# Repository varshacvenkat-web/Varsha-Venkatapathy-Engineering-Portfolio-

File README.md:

# Varsha-Venkatapathy-Engineering-Portfolio-
Portfolio of all projects done through my undergraduate and industry career:

**Biomedical Engineering | Machine Learning | Medical Device Innovation**

Portfolio of technical projects spanning **medical device development**, **deep learning applications**, and **hardware-embedded systems**. Work includes NSF-funded ultrasound imaging research, competitive scholarship projects, industry ML deployment, and FDA-pathway medical devices—demonstrating expertise across the full engineering stack from signal processing to production-ready systems.

**Highlights:**
-  **Medical Devices**: Self-charging pacemaker systems, real-time load monitoring for scoliosis treatment
-  **Machine Learning**: LSTM revenue forecasting (industry deployment), speech enhancement, medical image processing
-  **Research**: NSF-funded ultrasound imaging, Abrams Scholar project, multi-lab publications

*MS ECE Applicant | UNC Chapel Hill & NC State BME '25*

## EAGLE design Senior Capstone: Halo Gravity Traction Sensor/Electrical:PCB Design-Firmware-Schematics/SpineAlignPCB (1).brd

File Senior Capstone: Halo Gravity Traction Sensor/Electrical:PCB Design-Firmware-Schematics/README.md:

## Electrical, PCB Design, Firmware, and Schematics  
## Senior Capstone: Halo Gravity Traction Load Monitoring Device

This directory contains all electrical engineering components of the halo gravity traction load-monitoring system, including schematics, PCB design files, firmware, and reference circuit images. These files document the full electrical workflow from concept to implementation.

---

## Contents

## Electrical Schematic
**File:** Electrical Schematic.pdf  
A complete wiring diagram detailing all electrical connections for the load monitoring device.  
Includes:
- Load cell interface  
- HX711 amplifier wiring  
- Microcontroller I/O assignments  
- Power regulation and battery connections  
- Safety components and grounding strategy  

---

## Firmware
**File:** Fullcodefinal_copy_20250424150533.ino  
The final microcontroller firmware used to:
- Read load cell data via HX711  
- Apply calibration factors  
- Perform real-time signal filtering  
- Stream traction load to external devices  
- Log sensor values for testing and verification  

Written in Arduino C/C++ for rapid prototyping and device testing.

---

## PCB Design Files
These files correspond to the custom PCB developed for the traction load-monitoring system.

### Board Layout  
**File:** SpineAlignPCB (1).brd  
Includes:
- Component placement  
- Routing of analog and digital traces  
- Ground plane and power distribution  
- Mounting hole alignment for enclosure  

### Schematic Source  
**File:** SpineAlignPCB (1).sch  
Editable schematic source file for PCB manufacturing or revision.

---

## Reference Circuit Image
**File:** circuit (2).png  
Circuit image used during early prototyping and breadboard validation.  
Shows:
- Preliminary load cell + amplifier wiring  
- Pin mapping for MCU  
- Initial design considerations prior to final PCB creation  

---

## Design Considerations

### Signal Integrity
- Short trace lengths for low-noise analog signals  
- Dedicated analog ground routing  
- Shielding and filtering for load cell signals  

### Power Management
- Battery-powered operation  
- Onboard voltage regulation  
- Low-power microcontroller configuration  

### Safety and Reliability
- Reverse-polarity protection  
- Overcurrent considerations  
- Mechanical strain relief for cable connections  

---

## Firmware Overview

### Main Functions
- `readLoadCell()`: Retrieves calibrated weight values  
- `tare()`: Zeros load cell drift  
- `HX711.begin()`: Initializes ADC amplifier  
- `Serial.write()`: Streams continuous load values  

### Sampling Rate
Configured for stable real-time data acquisition without significant lag.

---

## Recommended Tools

To edit or view files:
- **EAGLE or KiCad** — for PCB `.brd` / `.sch` files  
- **Arduino IDE** — for `.ino` firmware  
- **Adobe/Preview** — to view PDF schematics  
- **Any image viewer** — for `.png` circuit references  

---

## Usage Guide

1. Review the Electrical Schematic for wiring details  
2. Use PCB files for manufacturing or revisions  
3. Flash firmware to microcontroller using Arduino IDE  
4. Validate sensor readings with circuit reference image  
5. Integrate PCB into mechanical enclosure

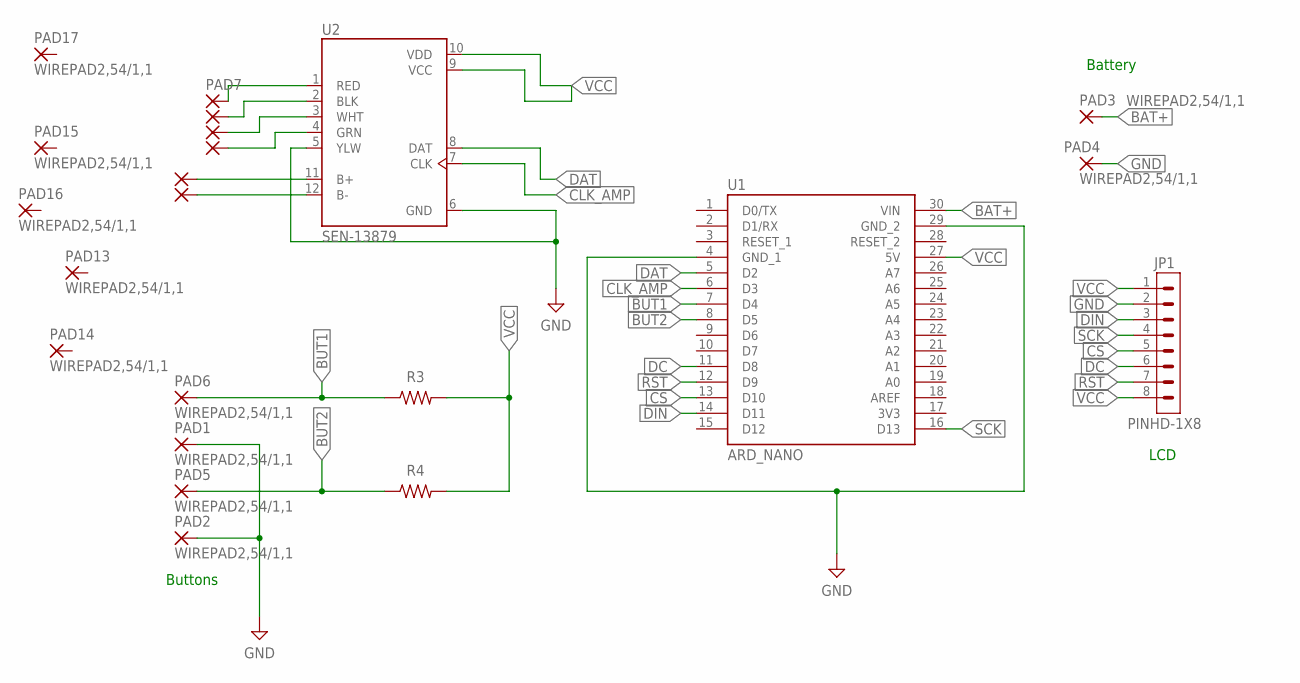
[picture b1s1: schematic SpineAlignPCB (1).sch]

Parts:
JP1: PINHD-1X8; 1X08
PAD1, PAD2, PAD3, PAD4, PAD5, PAD6, PAD7, PAD8, PAD9, PAD10, PAD11, PAD12, PAD13, PAD14, PAD15, PAD16, PAD17: WIREPAD2,54/1,1; 2,54/1,1
R3, R4: R-US_AXIAL-11.7MM-PITCH; RESAD1176W63L850D250B
U1: ARD_NANO; MODULE_A000005
U2: SEN-13879; SPARKFUN_SEN-13879

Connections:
3V3: U1.17 (3V3)
BAT+: PAD3.1, U1.30 (VIN)
BUT1: PAD6.1, R3.1, U1.7 (D4)
BUT2: PAD5.1, R4.1, U1.8 (D5)
CLK_AMP: U1.6 (D3), U2.7 (CLK)
CS: JP1.5, U1.13 (D10)
DAT: U1.5 (D2), U2.8 (DAT)
DC: JP1.6, U1.11 (D8)
DIN: JP1.3, U1.14 (D11)
GND: JP1.2, PAD1.1, PAD2.1, PAD4.1, U1.4 (GND_1), U1.29 (GND_2), U2.5 (YLW), U2.6 (GND)
unnamed: PAD7.1, U2.1 (RED)
unnamed: PAD8.1, U2.2 (BLK)
unnamed: PAD9.1, U2.3 (WHT)
unnamed: PAD10.1, U2.4 (GRN)
unnamed: PAD11.1, U2.11 (B+)
unnamed: PAD12.1, U2.12 (B-)
RST: JP1.7, U1.12 (D9)
SCK: JP1.4, U1.16 (D13)
VCC: JP1.1, JP1.8, R3.2, R4.2, U1.27 (5V), U2.9 (VCC), U2.10 (VDD)

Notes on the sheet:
LCD
Buttons
Battery

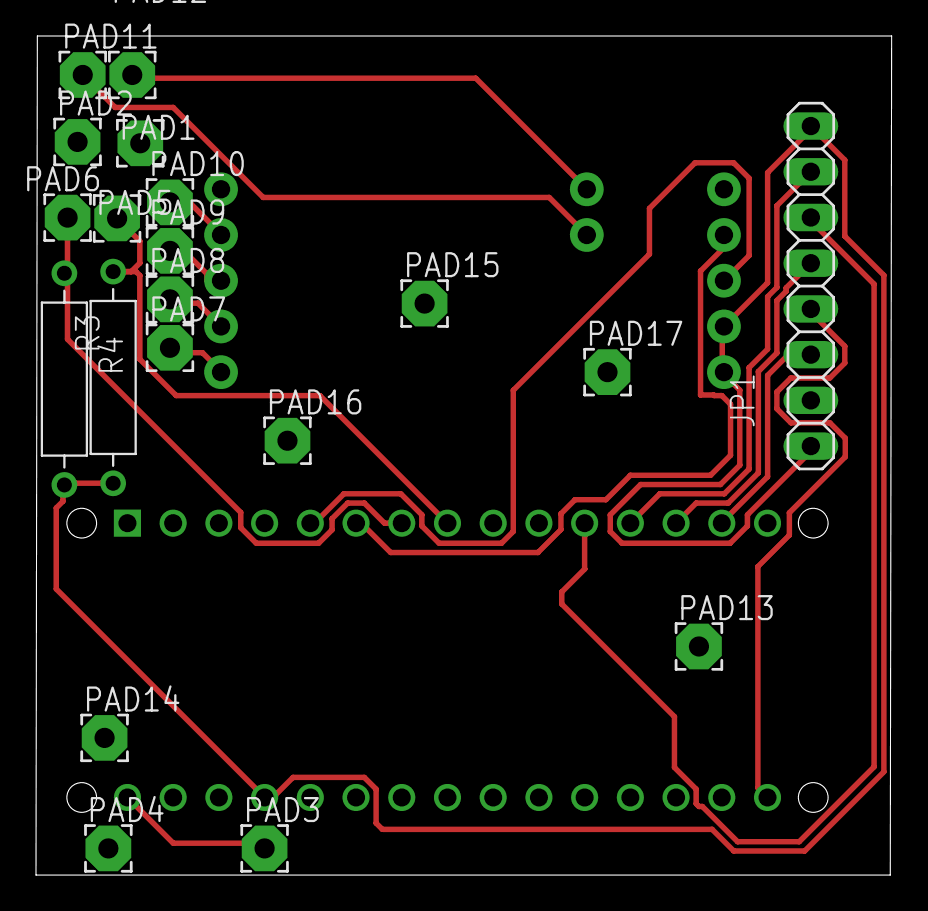
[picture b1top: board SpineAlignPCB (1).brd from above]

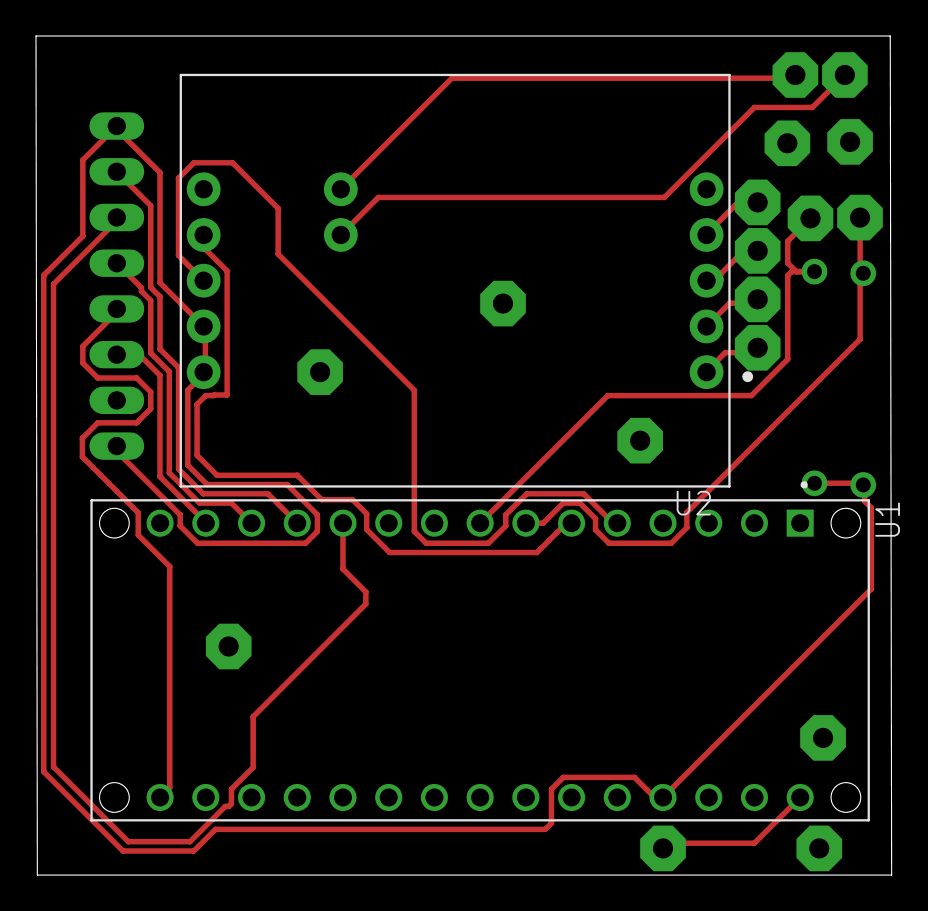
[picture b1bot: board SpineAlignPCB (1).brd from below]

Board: 2 copper layers, 47.5 x 46.6 mm, 22 parts (2 on the bottom side), 18 nets.

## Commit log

2025-11-26 Enhance README with project details and achievements
    Added detailed project overview, key achievements, technical implementation, preliminary results, and research impact sections to README.
2025-11-26 Created using Colab
2025-11-26 Rename Ultrasound_Tumor_Detection_Code_.ipynb to bmme-590-ultrasound/ Ultrasound_Tumor_Detection_Code_ipynb
2025-11-26 Create Deep Learning Speech Enhancement Abrams Scholar Project
2025-11-26 Add project overview for speech enhancement initiative
    This commit adds a comprehensive project overview for a speech enhancement initiative aimed at supporting hearing-impaired individuals using deep learning techniques. It includes details on model arc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
2025-11-26 Create Real-Time Deep Learning Speech Enhancement for Hearing-Impaired Patients
2025-11-26 Update print statement for loading trained weights
2025-11-26 Update README with code availability information
    Added section on code availability and model training details.
2025-11-26 Add Article_3_Babble.ipynb to legacy_split_noise
2025-11-26 Rename Article_3_Machinery.ipynb to preprocessing/legacy_split_noise/Article3Noise:Machinery
2025-11-26 Add Article_3_Traffic.ipynb to legacy split noise
2025-11-26 Rename Babble_Article_1.ipynb to preprocessing/Article1Noise:Babble
2025-11-26 Add Machinery_Article_1.ipynb to legacy split noise
2025-11-26 Add Traffic_Article_1.ipynb to legacy_split_noise
2025-11-26 Rename Preprocessing_Article_2.ipynb to preprocessing_all_noise/.gitkeep/Preprocessing_Article_2.ipynb
2025-11-26 Rename Preprocessing_article_1.ipynb to preprocessing_all_noise/Preprocessing_article_1.ipynb
2025-11-26 Rename Trafficarticle4 (1).ipynb to legacy_split_noise/Trafficarticle4.ipynb
2025-11-26 Rename article2_ipynb.ipynb to preprocessing_all_noise/article2_ipynb.ipynb
2025-11-26 Rename article_4_preprocessing.ipynb to preprocessing_all_noise/article_4_preprocessing.ipynb
2025-11-26 Rename preporcessing_3.ipynb to preprocessing_all_noise/preporcessing_3.ipynb
2025-11-26 Rename machinery article 4.ipynb to legacy_split_noise/machinery article 4.ipynb
2025-11-26 Rename preprocessing/Article1Noise:Babble to preprocessing/legacy_split_noise/Article1Noise:Babble
2025-11-26 Add Preprocessingarticle2 notebook
2025-11-26 Rename preprocessing_all_noise/Preprocessing_article_1.ipynb to preprocessing_all_noise/preprocessing/Preprocessing_article_1.ipynb
2025-11-26 Rename legacy_split_noise/Trafficarticle4.ipynb to Real-Time Deep Learning Speech Enhancement for Hearing-Impaired Patients/preprocessing/legacy_split_noise/Trafficarticle4.ipynb
2025-11-26 Rename legacy_split_noise/machinery article 4.ipynb to preprocessing/legacy_split_noise/machinery article 4.ipynb
2025-11-26 Add processing_article_1 notebook for noise preprocessing
2025-11-26 Rename processing_article_1.ipynb to preprocessingarticle1
2025-11-26 Rename preprocessing_all_noise/Preprocessingarticle2 to preprocessing/preprocessing_all_noise/Preprocessingarticle2
2025-11-26 Add preprocessingarticle2.ipynb for noise analysis
2025-11-26 Rename preprocessing_all_noise/article_4_preprocessing.ipynb to preprocessing/preprocessing_all_noise/article_4_preprocessing.ipynb
2025-11-26 Rename preprocessing_all_noise/preporcessing_3.ipynb to preprocessing/preprocessing_all_noise/preporcessing_3.ipynb
2025-11-26 Add CNN preprocessing for speech enhancement
2025-11-26 Add FCNN Model to preprocessing directory
2025-11-26 Add RNN model to preprocessing notebook
2025-11-26 Rename preprocessing/preprocessing_all_noise/preprocessingarticle1 to Real-Time Deep Learning Speech Enhancement/ preprocessing/ preprocessing_all_noise/CRNN Model
2025-11-26 Rename preprocessing/legacy_split_noise/Article1Noise:Babble to Real-Time Deep Learning Speech Enhancement/ preprocessing/ preprocessing_all_noise/ legacy_split_noise/CRNN-Babble
2025-11-26 Rename Article1Noise to CRNN: Machinery
2025-11-26 Rename preprocessing/legacy_split_noise/Article1Noise:Traffic to Real-Time Deep Learning Speech Enhancement/ preprocessing/ preprocessing_all_noise/ legacy_split_noise/CRNN:Traffic
2025-11-26 Update Article3Noise:Babble file path
2025-11-26 Rename Article3Noise to RNN: Machinery
2025-11-26 Update path for Article3Noise:Traffic
2025-11-26 Update machinery article in Jupyter notebook
2025-11-26 Add CNN model code for speech enhancement
2025-11-26 Rename preprocessing/preprocessing_all_noise/Real-Time Deep Learning Speech Enhancement/ CNN Model Code to Real-Time Deep Learning Speech Enhancement/CNN Model Code
2025-11-26 Rename Real-Time Deep Learning Speech Enhancement for Hearing-Impaired Patients/preprocessing/legacy_split_noise/Trafficarticle4.ipynb to Real-Time Deep Learning Speech Enhancement/ preprocessing/ pr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
2025-11-26 Add CNN Model for speech enhancement preprocessing
2025-11-26 Rename CNN Model to CNN Model.
2025-11-26 Rename CNN Model. to CNN Model
2025-11-26 Rename Real-Time Deep Learning Speech Enhancement/CNN Model Code to Real-Time Deep Learning Speech Enhancement/preprocessing/ preprocessing_all_noise/CNN Model Code
2025-11-26 Rename Real-Time Deep Learning Speech Enhancement/preprocessing/ preprocessing_all_noise/CNN Model Code to Real-Time Deep Learning Speech Enhancement/CNN Model Code
2025-11-26 Rename Preprocessing_Article_2.ipynb to CNN Model.ipynb
2025-11-26 Rename article_4_preprocessing.ipynb to FCNN Model.ipynb
2025-11-26 Add files via upload
    Title: Real-time single-channel deep neural network-based speech enhancement on edge devices
    Authors: Shankar, Bhat, Panahi (2020)
    Model Type: CRNN (Convolutional + RNN)
    Why:
    The paper explicitly describes a CRNN architecture combining CNN + LSTM layers
    Focuses on real-time smartphone implementation
2025-11-26 Rename nihms-1632641 (4).pdf to CNNReference.pdf
2025-11-26 Rename CNNReference.pdf to CRNNReference.pdf
2025-11-26 Rename 389_1_online (5).pdf to RNN.pdf
2025-11-26 Create BMME575:Practical Machine Learning Final Project: Fetal Ultrasound Image Denoising Using Lightweight Attention Networks
2025-11-26 Rename Final Delivery Presentation - BMME 575 - Nalaya, Matthew, Enakshi, Varsha.pdf to Final Delivery Presentation - BMME 575 - Varsha, Matthew, Enakshi, Nalaya.pdf
2025-11-26 Rename Final Report - BMME 575 - Enakshi, Nalaya, Varsha, Matthew (Wu) Zehao.pdf to Final Report - BMME 575 - Varsha, Nalaya, Enakshi, Matthew (Wu) Zehao.pdf
2025-11-26 Rename Final_Delivery_Code_BMME_575_Enakshi,_Nalaya,_Varsha,_Wu_(Matthew) (1).ipynb to Final_Delivery_Code_BMME_575_Varsha,_Nalaya,_Enakshi,_Wu_(Matthew) (1).ipynb
2025-11-26 Rename README.md to README.md
2025-11-26 Rename Slides of Anisotropy Phantoms for Varsha (1).pdf to Slides of Anisotropy Phantoms.pdf
2025-11-26 Rename Abrams Scholar Poster 51.pdf to Abrams Scholar Poster .pdf
2025-11-26 Rename Final 10_00 IEEE Paper Format.docx (1).pdf to Final IEEE Paper Format.docx (1).pdf
2025-11-26 Create Senior Capstone: Halo Gravity Sensor
2025-11-26 Rename Senior Capstone: Halo Gravity Traction Sensor/Mechanical_CADfiles.md to Senior Capstone: Halo Gravity Traction Sensor/Mechanical_CAD/README.md
2025-11-26 Rename Póster educativo Funciones e importancia de los océanos biología ilustrativo azul.pdf.pdf to Halo Gravity Traction poster.pdf
